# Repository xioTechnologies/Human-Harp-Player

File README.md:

Human-Harp-Player
=================

The Human Harp Player is a music controller based on interaction with an extendible cord under constant tension.  The Player provides measurements of the cord: extension, velocity, angle (azimuth and elevation) and angular rate (for detecting plucks).  The Player incorporates an [x-OSC](http://www.x-io.co.uk/x-osc/) to interface to host software via Wi-Fi.

Counts vary between 7800 counts/m and 1000 counts/m when fully extended, average = 8900.

See [Human Harp](http://humanharp.org/) for more information about the project.

PCB
---

The PCB was designed in [EAGLE Version 6.6](http://www.cadsoftusa.com/).  It was fabricated by [OSH Park](https://oshpark.com/) and is available to [purchase on their site](https://oshpark.com/shared_projects/F7BSWUvG).

Firmware
--------

The Human Harp Player uses a Microchip [dsPIC33EP512GM604](http://www.microchip.com/wwwproducts/Devices.aspx?product=dsPIC33EP512GM604) 16-bit [DSC](http://en.wikipedia.org/wiki/Digital_signal_controller) running at 140 MHz (70 MIPS).  The firmware was developed using Microchip's free [MPLABX IDE v2.15](http://www.microchip.com/pagehandler/en-us/family/mplabx/) and [XC16 v1.21 C compiler](http://www.microchip.com/pagehandler/en_us/devtools/mplabxc/).  The PCB incorporates an ICSP header compatible with Microchip programming tools such as the [PICkit 3](http://www.microchip.com/Developmenttools/ProductDetails.aspx?PartNO=PG164130) or [ICD 3](http://www.microchip.com/Developmenttools/ProductDetails.aspx?PartNO=DV164035).

Test App
--------

The Human Harp Player Test App is a cross-platform application for visualising measurement data (distance, velocity, azimuth, elevation and angular rate) in real-time using [Processing](http://www.processing.org/).  Messages from the Player ("Reset", "Zero", "Sleep", "Firmware: vX.X") are displayed in the output console.  Clicking the window sends a 'zero' command.

The Processing sketch requires the [oscP5 library](http://www.sojamo.de/libraries/oscP5/) to send and receive OSC messages.  To use this library, copy the entire *oscP5* directory (.zip available in the repository) into a directory named *"libraries"* in Processing Sketchbook location (see: *File* > *Preferences* > *Sketchbook location*).  A tutorial for sending and receiving OSC messages in Processing is available on the [codasign](http://learning.codasign.com/index.php?title=Sending_and_Receiving_OSC_Data_Using_Processing) website.

**Windows 7 Firewall:**  When running the processing application for the first time you will be prompted to grant network access to Java by Windows Firewall.  Java must be given access "Public" access else network communication will not be possible.  These permission can be modified any time through *Control Panel* > *Windows Firewall* > *"Change settings"*.

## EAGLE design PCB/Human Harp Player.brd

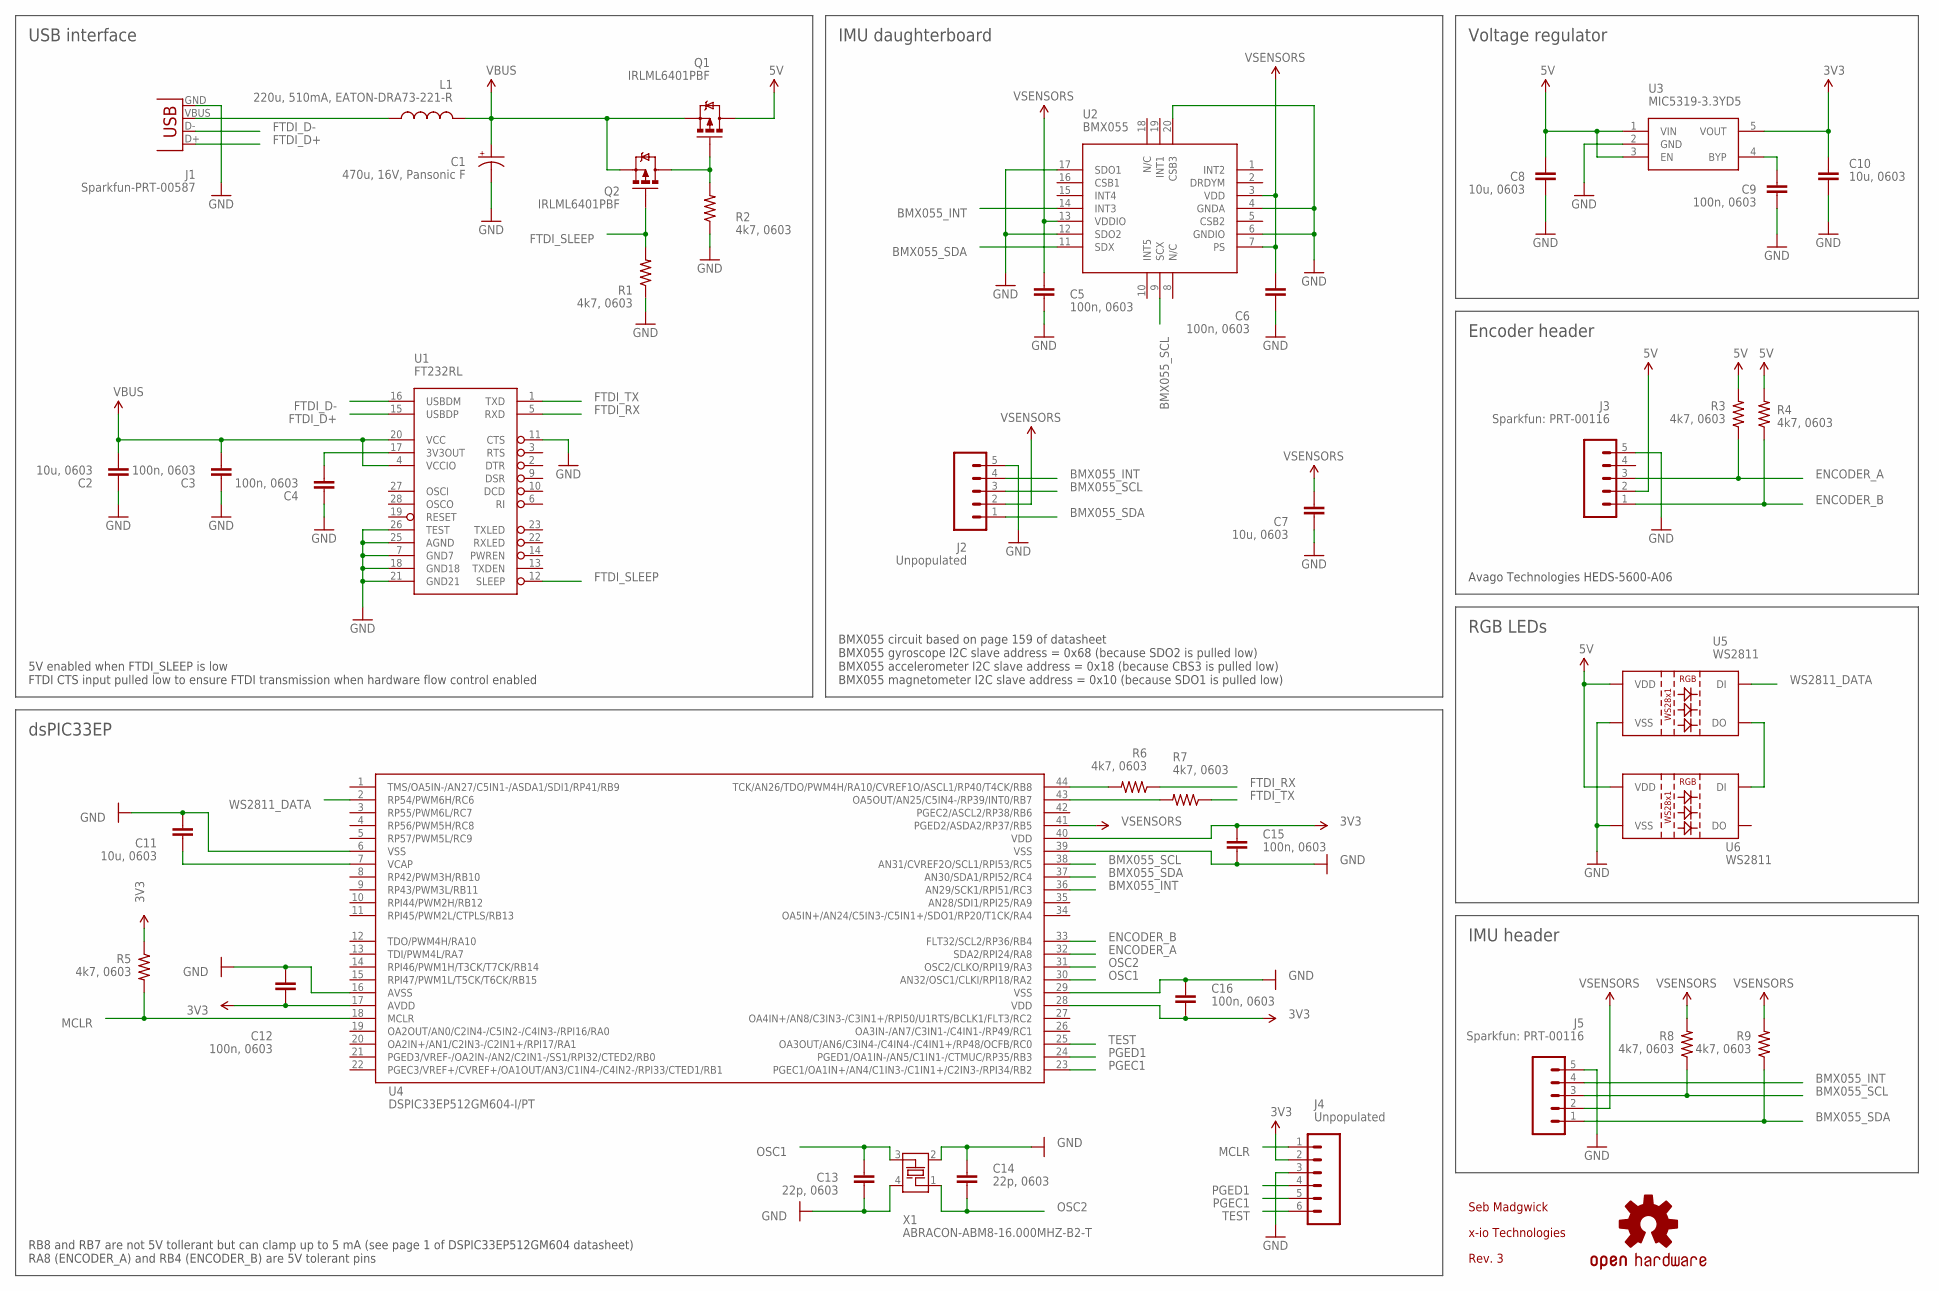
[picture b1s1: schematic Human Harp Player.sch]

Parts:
C1: 470u, 16V, Pansonic F; PANASONIC_F
C2, C7, C8, C10, C11: 10u, 0603; 0402-CAP
C3, C4, C5, C6, C9, C12, C15, C16: 100n, 0603; 0402-CAP
C13, C14: 22p, 0603; 0402-CAP
J1: Sparkfun-PRT-00587; USB-MINIB
J2: Unpopulated; 1X05
J3, J5: Sparkfun: PRT-00116; 1X05
J4: Unpopulated; 1X06_NO_SILK
L1: 220u, 510mA, EATON-DRA73-221-R; PIS2816
LOGO1: OSHW-LOGOL; OSHW-LOGO-L
Q1, Q2: IRLML6401PBF; SOT23-3
R1, R2, R3, R4, R5, R6, R7, R8, R9: 4k7, 0603; 0402-RES
U1: FT232RL; SSOP28DB
U2: BMX055
U3: MIC5319-3.3YD5; SOT23-5
U4: DSPIC33EP512GM604-I/PT; TQFP44
U5, U6: WS2811; LED-TRICOLOR-5050-IC
X1: ABRACON-ABM8-16.000MHZ-B2-T; ABM8

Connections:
3V3: C10.1, C12.1, C15.1, C16.2, J4.2, R5.1, U3.5 (VOUT), U4.17 (AVDD), U4.28 (VDD), U4.40 (VDD)
5V: C8.1, J3.2, Q1.3 (D), R3.2, R4.2, U3.1 (VIN), U3.3 (EN), U5.3 (VDD), U5.5 (VDD), U6.3 (VDD), U6.5 (VDD)
BMX055_INT: J2.4, J5.4, U2.14 (INT3), U4.36 (AN29/SCK1/RPI51/RC3)
BMX055_SCL: J2.3, J5.3, R8.1, U2.9 (SCX), U4.38 (AN31/CVREF2O/SCL1/RPI53/RC5)
BMX055_SDA: J2.1, J5.1, R9.1, U2.11 (SDX), U4.37 (AN30/SDA1/RPI52/RC4)
ENCODER_A: J3.3, R3.1, U4.32 (SDA2/RPI24/RA8)
ENCODER_B: J3.1, R4.1, U4.33 (FLT32/SCL2/RP36/RB4)
FTDI_D+: J1.D+, U1.15 (USBDP)
FTDI_D-: J1.D-, U1.16 (USBDM)
FTDI_RX: R6.1, U1.5 (RXD)
FTDI_SLEEP: Q2.1 (G), R1.2, U1.12 (SLEEP)
FTDI_TX: R7.1, U1.1 (TXD)
GND: C1.-, C2.1, C3.1, C4.1, C5.2, C6.2, C7.1, C8.2, C9.2, C10.2, C11.2, C12.2, C13.1, C14.1, C15.2, C16.1, J1.GND, J2.5, J3.5, J4.3, J5.5, R1.1, R2.1, U1.7 (GND7), U1.11 (CTS), U1.18 (GND18), U1.21 (GND21), U1.25 (AGND), U1.26 (TEST), U2.4 (GNDA), U2.6 (GNDIO), U2.12 (SDO2), U2.17 (SDO1), U2.20 (CSB3), U3.2 (GND), U4.6 (VSS), U4.16 (AVSS), U4.29 (VSS), U4.39 (VSS), U5.6 (VSS), U6.6 (VSS), X1.2, X1.4
MCLR: J4.1, R5.2, U4.18 (MCLR)
unnamed: Q1.1 (G), Q2.3 (D), R2.2
unnamed: R6.2, U4.44 (TCK/AN26/TDO/PWM4H/RA10/CVREF1O/ASCL1/R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)
unnamed: C4.2, U1.17 (3V3OUT)
unnamed: C11.1, U4.7 (VCAP)
unnamed: R7.2, U4.43 (OA5OUT/AN25/C5IN4-/RP39/INT0/RB7)
unnamed: J1.VBUS, L1.1
unnamed: C9.1, U3.4 (BYP)
unnamed: U5.1 (DO), U6.2 (DI)
OSC1: C13.2, U4.30 (AN32/OSC1/CLKI/RPI18/RA2), X1.3
OSC2: C14.2, U4.31 (OSC2/CLKO/RPI19/RA3), X1.1
PGEC1: J4.5, U4.23 (PGEC1/OA1IN+/AN4/C1IN3-/C1IN1+/C2IN3-/R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)
PGED1: J4.4, U4.24 (PGED1/OA1IN-/AN5/C1IN1-/CTMUC/RP35/RB3)
TEST: J4.6, U4.25 (OA3OUT/AN6/C3IN4-/C4IN4-/C4IN1+/RP48/OC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)
VBUS: C1.+, C2.2, C3.2, L1.2, Q1.2 (S), Q2.2 (S), U1.4 (VCCIO), U1.20 (VCC)
VSENSORS: C5.1, C6.1, C7.2, J2.2, J5.2, R8.2, R9.2, U2.3 (VDD), U2.7 (PS), U2.13 (VDDIO), U4.41 (PGED2/ASDA2/RP37/RB5)
WS2811_DATA: U4.2 (RP54/PWM6H/RC6), U5.2 (DI)

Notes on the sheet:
Voltage regulator
Seb Madgwick
x-io Technologies
dsPIC33EP
Encoder header
IMU header
IMU daughterboard
USB interface
Avago Technologies HEDS-5600-A06
5V enabled when FTDI_SLEEP is low FTDI CTS input pulled low to ensure FTDI transmission when hardware flow control enabled
BMX055 circuit based on page 159 of datasheet BMX055 gyroscope I2C slave address = 0x68 (because SDO2 is pulled low) BMX055 accelerometer I2C slave address = 0x18 (because CBS3 is pulled low) BMX055 magnetometer I2C slave address = 0x10 (because SDO1 is pulled low)
RGB LEDs
RB8 and RB7 are not 5V tollerant but can clamp up to 5 mA (see page 1 of DSPIC33EP512GM604 datasheet) RA8 (ENCODER_A) and RB4 (ENCODER_B) are 5V tolerant pins
Rev. 3

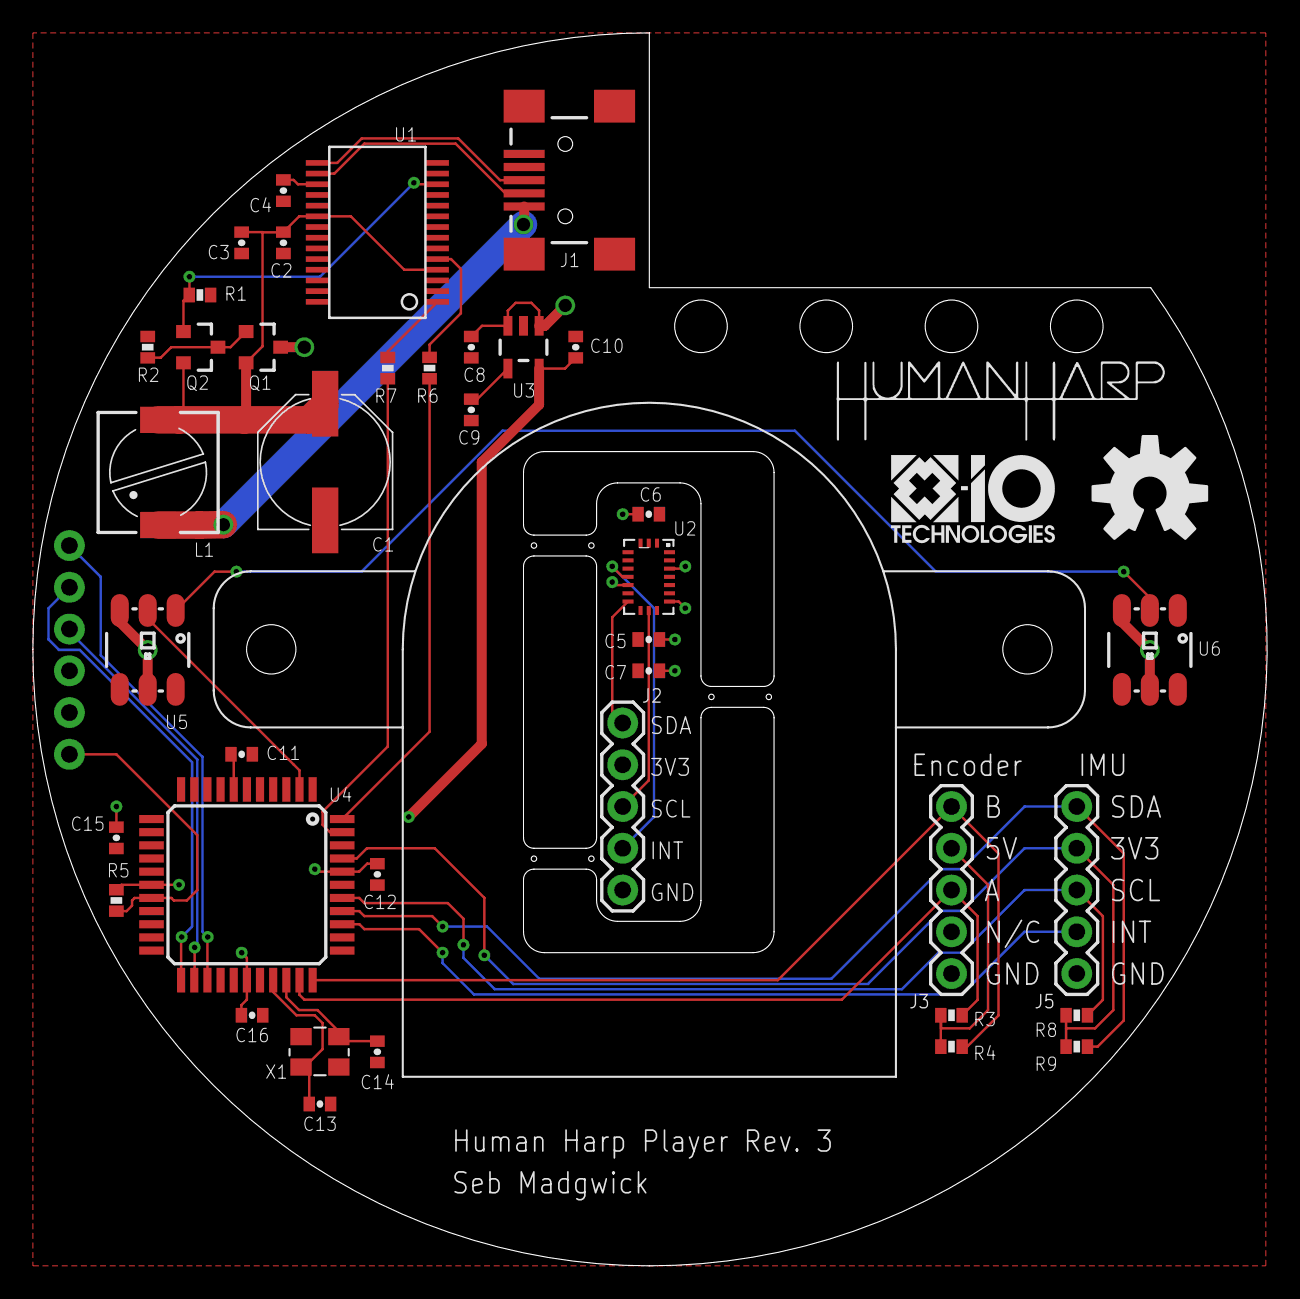
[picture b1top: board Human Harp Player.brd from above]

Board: 2 copper layers, 75.1 x 75.0 mm, 44 parts (0 on the bottom side), 30 nets.

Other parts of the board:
U$1: X-IO_TECHNOLOGIES_LOGO_10MM_TOP
U$2: HEDS-5600-A06
U$4: HUMAN_HARP_LOGO_20MM_TOP

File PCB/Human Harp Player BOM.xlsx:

Parts | Qty | Value
C3, C4, C5, C6, C9, C12, C15, C16 | 8 | 100n, 0603
C2, C7, C8, C10, C11 | 5 | 10u, 0603
L1 | 1 | 220u, 510mA, EATON-DRA73-221-R
C13, C14 | 2 | 22p, 0603
C1 | 1 | 470u, 16V, Pansonic F
R1, R2, R3, R4, R5, R6, R7, R8, R9 | 9 | 4k7, 0603
X1 | 1 | ABRACON-ABM8-16.000MHZ-B2-T
U2 | 1 | BMX055
U4 | 1 | DSPIC33EP512GM604-I/PT
U1 | 1 | FT232RL
Q1, Q2 | 2 | IRLML6401PBF
U3 | 1 | MIC5319-3.3YD5
J1 | 1 | Sparkfun-PRT-00587
J3, J5 | 2 | Sparkfun: PRT-00116
J2, J4 | 1 | Unpopulated
U5, U6 | 2 | WS2811

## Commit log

2014-07-18 Commit PCB project files
2014-07-22 Commit firmware project files
2014-07-22 Commit Test App project files
2014-07-23 Add screenshot
2014-07-23 Remove code artifacts in encoder initialisation
2014-07-23 Fix bug that causes infinite loop just before sleep
2014-07-24 Switch encoder A/B signals in firmware
2014-07-24 Reduce send rate to 50 Hz
2014-07-25 Test App indicates battery voltage
2014-07-25 Send firmware version on start up
2014-07-25 Show messages in Test App output console
2014-07-25 Add missing file FirmwareVersion.h
2014-07-25 Implment quick solution for remote 'zero' command
2014-07-29 Indicate as firmware v1.0
2014-08-04 Add PCB photos
2015-03-02 Commit all changes prior to 2015
2015-03-02 Commit PCB Rev. 2
2015-03-09 Add missing VDD connection to ICSP and XYZ label on PCB
2015-03-09 Remove unused code from Firmware for PCB Rev. 2
2015-03-09 Contain all clock and I/O definitions in SystemDefinitions.h
2015-03-09 Remove GenericTypeDefs.h
2015-03-09 Add missing SystemDefinitions.h
2015-03-09 Use latest UART library an implement RX commands
2015-03-09 Test App uses serial port instead of UDP
2015-03-09 Use latest I2C library
2015-03-09 Use latest Timer library
2015-03-10 Tidy up Encoder, IMU, Send and Receive modules
2015-03-10 Add family reference manuals cited in firmware comments
2015-03-19 Remove unnecessary delays
2015-03-19 Update gitignore and clean-up .bat file
2015-04-14 Fix I2C ACK/NACK bug and use latest compiler

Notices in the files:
parts and their libraries:
SparkFun-Connectors: Licensing: Creative Commons ShareAlike 4.0 International - https://creativecommons.org/licenses/by-sa/4.0
